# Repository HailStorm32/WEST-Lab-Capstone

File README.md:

## About

### Summary
This repo houses the code, board files, CAD files and documents for the SCuM observatory.

The SCuM observatory is designed as a portable platform that accommodates a SCuM breakout board alongside various measurement devices. These devices provide direct access to the SCuM’s I/O, enabling power control and monitoring, digital and analog pin stimulation/measurement, RF stimulation/measurement, and programming. All communication with the observatory, including control of its measurement devices, occurs through a single USB cable. A Python scripting interface is used for high-level interactions with the observatory and its hardware.

### Contributors
| Name                  |
|-----------------------|
| [Alex Jain](https://github.com/ajainPSU)   |
| [Demetri Van Sickle](https://github.com/HailStorm32) |
| [John Yang](https://github.com/yan7-psu)  |
| [Mitch Montee](https://github.com/mmontee)  |
|[Nate Sjullie](https://github.com/nsjullie) |

<br>

<br>

## Setup

Please see [The Wiki](https://github.com/HailStorm32/WEST-Lab-Capstone/wiki/2.0-Setup)

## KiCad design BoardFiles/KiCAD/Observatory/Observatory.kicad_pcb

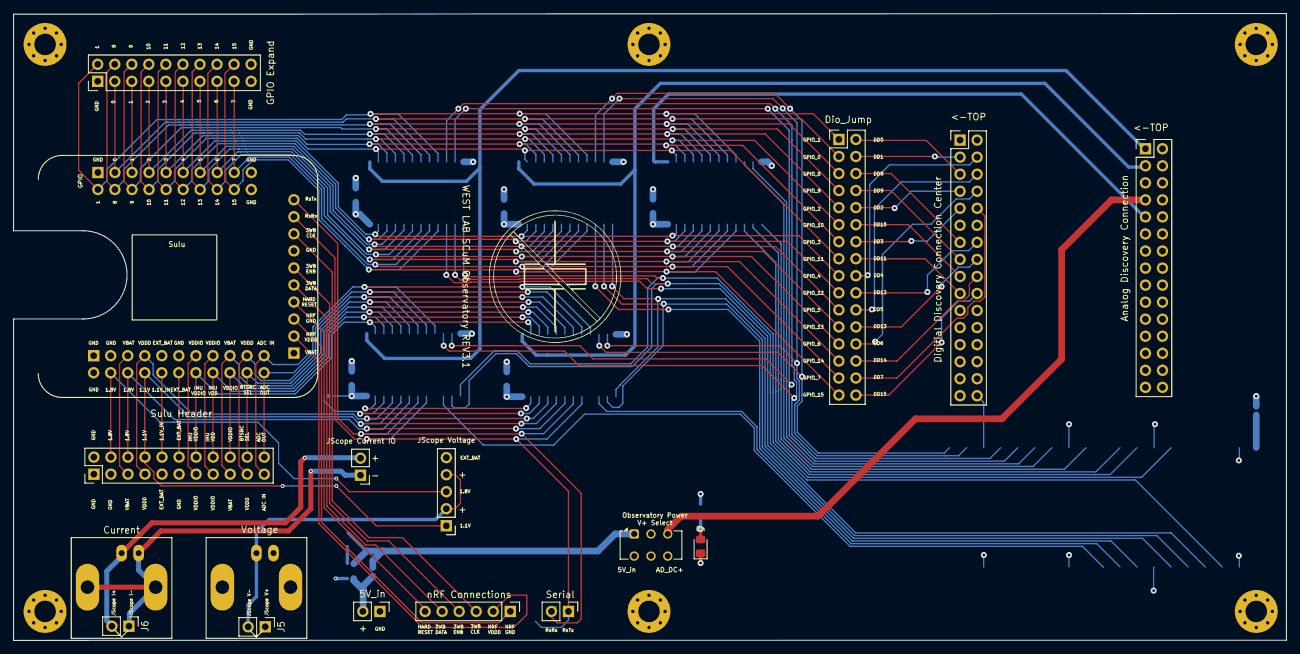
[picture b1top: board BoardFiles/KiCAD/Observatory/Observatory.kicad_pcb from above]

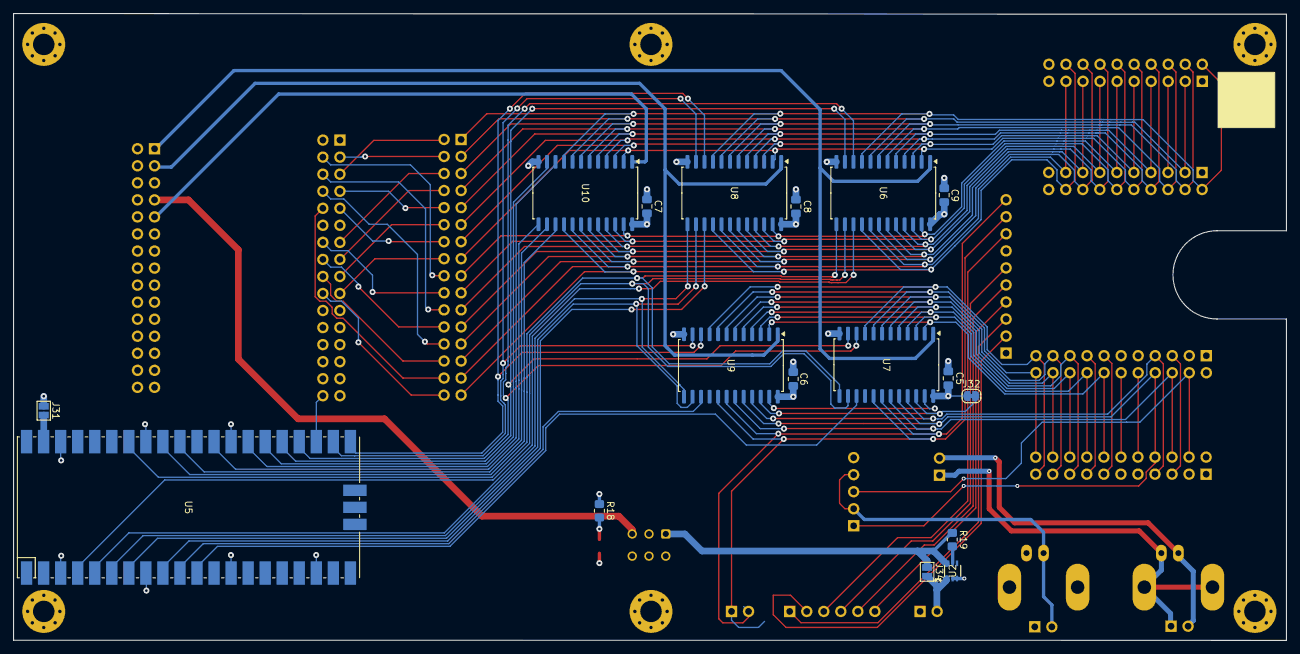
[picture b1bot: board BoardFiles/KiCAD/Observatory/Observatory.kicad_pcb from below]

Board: 4 copper layers, 189.7 x 93.4 mm, 40 parts (17 on the bottom side), 90 nets.

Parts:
C5, C6, C7, C8, C9: C; C_0805_2012Metric_Pad1.18x1.45mm_HandSolder
D1: LED; LED_0805_2012Metric_Pad1.15x1.40mm_HandSolder
J2: Analog Discovery Connection; PinHeader_2x15_P2.54mm_Vertical
J3: Digitial Discovery Connection Center; PinHeader_2x16_P2.54mm_Vertical
J4: GPIO Expand; PinHeader_2x10_P2.54mm_Vertical
J5: JScope V; PinHeader_1x02_P2.54mm_Vertical
J6: JScope I; PinHeader_1x02_P2.54mm_Vertical
J8: JScope Current IO; PinHeader_1x02_P2.54mm_Vertical
J9: 5V_in; PinHeader_1x02_P2.54mm_Vertical
J10: Dio_Jump; PinHeader_2x16_P2.54mm_Vertical
J11: nRF Connections; PinHeader_1x06_P2.54mm_Vertical
J12: Sulu Header; PinHeader_2x11_P2.54mm_Vertical
J13: Serial; PinHeader_1x02_P2.54mm_Vertical
J16: JScope Voltage; PinHeader_1x05_P2.54mm_Vertical
J20, J21, J22, J23, J36, J37: Mounting Hole; MountingHole_3.2mm_M3_Pad_Via
J24: Observatory PWR; SW_CK_JS202011CQN_DPDT_Straight
J30, J33: Conn_Coaxial_Small; BNC_Amphenol_B6252HB-NPP3G-50_Horizontal
J31, J34: Jumper; SolderJumper-2_P1.3mm_Open_Pad1.0x1.5mm
J32: Jumper; SolderJumper-2_P1.3mm_Bridged_RoundedPad1.0x1.5mm
R18: R; R_0805_2012Metric_Pad1.20x1.40mm_HandSolder
R19: R_st; R_0805_2012Metric_Pad1.20x1.40mm_HandSolder
U1: 1; SuLu_Foot
U2: LM66100DCKR
U5: Pico; RPi_Pico_SMD_TH
U6, U7, U8, U9, U10: CD74HC4067M; SOIC-24W_7.5x15.4mm_P1.27mm

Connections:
+5V: C5.1, C6.1, C7.1, C8.1, C9.1, J12.9, J12.12, J16.5, J24.2, J31.1, J32.1, R18.1, U1.9c (EXT_BAT), U1.12c (EXT_BAT), U6.24 (VCC), U7.24 (VCC), U8.24 (VCC), U9.24 (VCC), U10.24 (VCC)
AD_DC_Supply+: J2.7, J24.3
AD_Scope1+: J2.1, U6.1 (COM), U7.1 (COM)
AD_Scope1-: C5.2, C6.2, C7.2, C8.2, C9.2, D1.1 (K), J2.2, J2.4, J2.5, J2.6, J2.11, J2.12, J3.1, J3.2, J3.11, J3.12, J3.21, J3.22, J3.31, J3.32, J4.1, J4.19, J4.20, J5.1, J9.1, J12.1, J12.2, J12.3, J12.11, J20.1, J21.1, J22.1, J23.1, J33.2 (Ext), J36.1, J37.1, U1.1a (GND), U1.1c (GND), U1.2c (GND), U1.3c (GND), U1.7b (GND), U1.11c (GND), U1.19a (GND), U1.20a (GND), U2.2 (GND), U2.3 (*CE), U5.3 (GND), U5.8 (GND), U5.13 (GND), U5.18 (GND), U5.23 (GND), U5.28 (GND), U5.33 (AGND), U5.38 (GND), U6.12 (GND), U7.12 (GND), U8.12 (GND), U9.12 (GND), U10.12 (GND)
AD_Scope2+: J2.3, U8.1 (COM), U9.1 (COM)
AD_WaveGen1: J2.9, U10.1 (COM)
DD_DIN_0: J3.3, J10.4
DD_DIN_1: J3.5, J10.2
DD_DIN_2: J3.7, J10.10
DD_DIN_3: J3.9, J10.14
DD_DIN_4: J3.4, J10.18
DD_DIN_5: J3.6, J10.22
DD_DIN_6: J3.8, J10.26
DD_DIN_7: J3.10, J10.30
DD_DIN_8: J3.13, J10.6
DD_DIN_9: J3.15, J10.8
DD_DIN_10: J3.17, J10.12
DD_DIN_11: J3.19, J10.16
DD_DIN_12: J3.14, J10.20
DD_DIN_13: J3.16, J10.24
DD_DIN_14: J3.18, J10.28
DD_DIN_15: J3.20, J10.32
JS_I+: J6.2, J8.2, J30.1 (In)
JS_I-: J6.1, J8.1, J30.2 (Ext)
JS_V+: J5.2, J16.2, J16.4, J33.1 (In)
unnamed: D1.2 (A), R18.2
unnamed: J4.5, U1.5a (GPIO1)
unnamed: J11.1, U1.3b (NRF_GND)
unnamed: J11.2, U1.2b (NRF_VDDD)
unnamed: J11.3, U1.8b (3WB_CLK)
unnamed: J11.4, U1.6b (3WB_ENB)
unnamed: J11.5, U1.5b (3WB_DATA)
unnamed: J11.6, U1.4b (HARD_RESET)
unnamed: J12.4, J16.3, U1.4c (1.8V)
unnamed: J12.5, U1.5c (VBAT)
unnamed: J12.10, U1.10c (1.1V_IN)
unnamed: J12.13, U1.13c (VDDIO)
unnamed: J12.15, U1.15c (VDDIO)
unnamed: J24.1, J34.1, R19.1, U2.6 (VOUT)
unnamed: J31.2, U5.39 (VSYS)
unnamed: J9.2, J34.2, U2.1 (VIN)
unnamed: R19.2, U2.5 (ST)
Scope 1 Mux 1: J4.2, J10.1, U1.2a (GPIO1), U6.9 (I0), U8.9 (I0), U10.9 (I0)
Scope 1 Mux 2: J4.3, J10.3, U1.3a (GPIO0), U6.8 (I1), U8.8 (I1), U10.8 (I1)
Scope 1 Mux 3: J4.4, J10.5, U1.4a (GPIO8), U6.7 (I2), U8.7 (I2), U10.7 (I2)
Scope 1 Mux 4: J4.6, J10.7, U1.6a (GPIO9), U6.6 (I3), U8.6 (I3), U10.6 (I3)
Scope 1 Mux 5: J4.7, J10.9, U1.7a (GPIO2), U6.5 (I4), U8.5 (I4), U10.5 (I4)
Scope 1 Mux 6: J4.8, J10.11, U1.8a (GPIO10), U6.4 (I5), U8.4 (I5), U10.4 (I5)
Scope 1 Mux 7: J4.9, J10.13, U1.9a (GPIO3), U6.3 (I6), U8.3 (I6), U10.3 (I6)
Scope 1 Mux 8: J4.10, J10.15, U1.10a (GPIO11), U6.2 (I7), U8.2 (I7), U10.2 (I7)
Scope 1 Mux 9: J4.11, J10.17, U1.11a (GPIO4), U6.23 (I8), U8.23 (I8), U10.23 (I8)
Scope 1 Mux 10: J4.12, J10.19, U1.12a (GPIO12), U6.22 (I9), U8.22 (I9), U10.22 (I9)
Scope 1 Mux 11: J4.13, J10.21, U1.13a (GPIO5), U6.21 (I10), U8.21 (I10), U10.21 (I10)
Scope 1 Mux 12: J4.14, J10.23, U1.14a (GPIO13), U6.20 (I11), U8.20 (I11), U10.20 (I11)
Scope 1 Mux 13: J4.15, J10.25, U1.15a (GPIO6), U6.19 (I12), U8.19 (I12), U10.19 (I12)
Scope 1 Mux 14: J4.16, J10.27, U1.16a (GPIO14), U6.18 (I13), U8.18 (I13), U10.18 (I13)
Scope 1 Mux 15: J4.17, J10.29, U1.17a (GPIO7), U6.17 (I14), U8.17 (I14), U10.17 (I14)
Scope 1 Mux 16: J4.18, J10.31, U1.18a (GPIO15), U6.16 (I15), U8.16 (I15), U10.16 (I15)
Scope 1 Mux 17: J12.21, U1.21c (ADC_IN), U7.9 (I0), U9.9 (I0)
Scope 1 Mux 18: J12.22, U1.22c (ADC_OUT), U7.8 (I1), U9.8 (I1)
Scope 1 Mux 19: J12.19, U1.19c (VDDD), U7.7 (I2), U9.7 (I2)
Scope 1 Mux 20: J12.20, U1.20c (BTSRC_SEL), U7.6 (I3), U9.6 (I3)
Scope 1 Mux 21: J12.17, U1.17c (VBAT), U7.5 (I4), U9.5 (I4)
Scope 1 Mux 22: J12.18, U1.18c (VDDIO), U7.4 (I5), U9.4 (I5)
Scope 1 Mux 23: J12.16, U1.16c (IMU_VDD), U7.3 (I6), U9.3 (I6)
Scope 1 Mux 24: J12.14, U1.14c (IMU_VDDIO), U7.2 (I7), U9.2 (I7)
Scope 1 Mux 25: U7.23 (I8), U9.23 (I8)
Scope 1 Mux 26: J32.2, U7.22 (I9), U9.22 (I9)
Scope 1 Mux 27: J12.7, U1.7c (VDDD), U7.21 (I10), U9.21 (I10)
Scope 1 Mux 28: J12.8, J16.1, U1.8c (1.1V), U7.20 (I11), U9.20 (I11)
Scope 1 Mux 29: J12.6, U1.6c (1.8V), U7.19 (I12), U9.19 (I12)
Scope 1 Mux 30: J13.2, U1.10b (RsTx), U7.18 (I13), U9.18 (I13)
Scope 1 Mux 31: J13.1, U1.9b (RsRx), U7.17 (I14), U9.17 (I14)
Scope 1 Mux Control 0: U5.24 (GPIO18), U6.10 (S0), U7.10 (S0)
Scope 1 Mux Control 1: U5.25 (GPIO19), U6.11 (S1), U7.11 (S1)
Scope 1 Mux Control 2: U5.4 (GPIO2), U6.14 (S2), U7.14 (S2)
Scope 1 Mux Control 3: U5.34 (GPIO28_ADC2), U6.13 (S3), U7.13 (S3)
Scope 1 Mux ~EN_A: U5.5 (GPIO3), U6.15 (~E)
Scope 1 Mux ~EN_B: U5.11 (GPIO8), U7.15 (~E)
Scope 2 Mux Control 0: U5.21 (GPIO16), U8.10 (S0), U9.10 (S0)
Scope 2 Mux Control 1: U5.22 (GPIO17), U8.11 (S1), U9.11 (S1)
Scope 2 Mux Control 2: U5.7 (GPIO5), U8.14 (S2), U9.14 (S2)
Scope 2 Mux Control 3: U5.6 (GPIO4), U8.13 (S3), U9.13 (S3)
Scope 2 Mux ~EN_A: U5.9 (GPIO6), U8.15 (~E)
Scope 2 Mux ~EN_B: U5.10 (GPIO7), U9.15 (~E)
WaveGen. 1 Mux ~EN: U5.32 (GPIO27_ADC1), U10.15 (~E)
WaveGen. Mux Control 0: U5.27 (GPIO21), U10.10 (S0)
WaveGen. Mux Control 1: U5.26 (GPIO20), U10.11 (S1)
WaveGen. Mux Control 2: U5.31 (GPIO26_ADC0), U10.14 (S2)
WaveGen. Mux Control 3: U5.29 (GPIO22), U10.13 (S3)

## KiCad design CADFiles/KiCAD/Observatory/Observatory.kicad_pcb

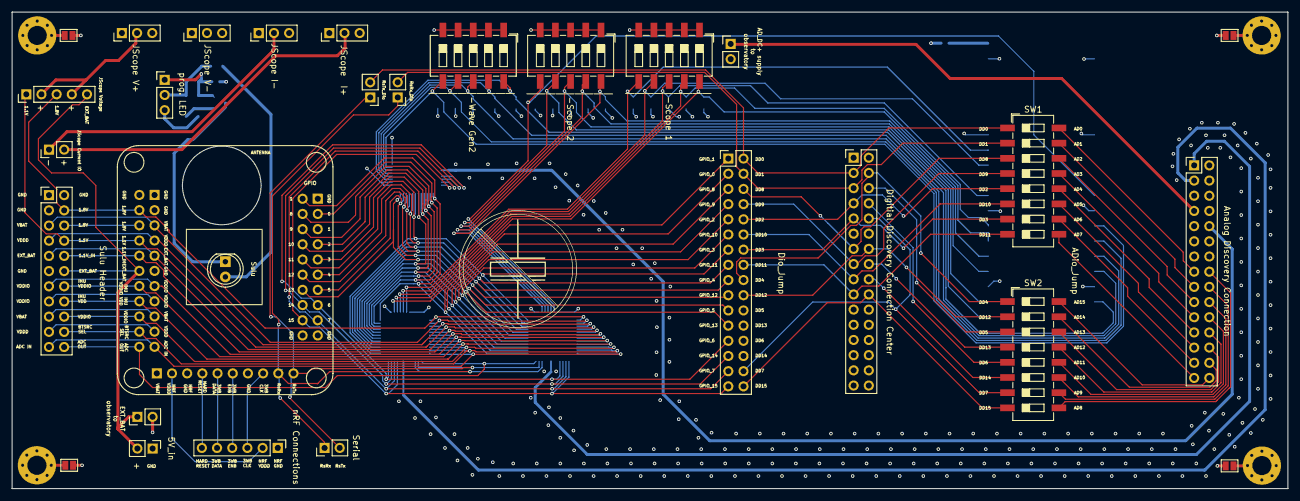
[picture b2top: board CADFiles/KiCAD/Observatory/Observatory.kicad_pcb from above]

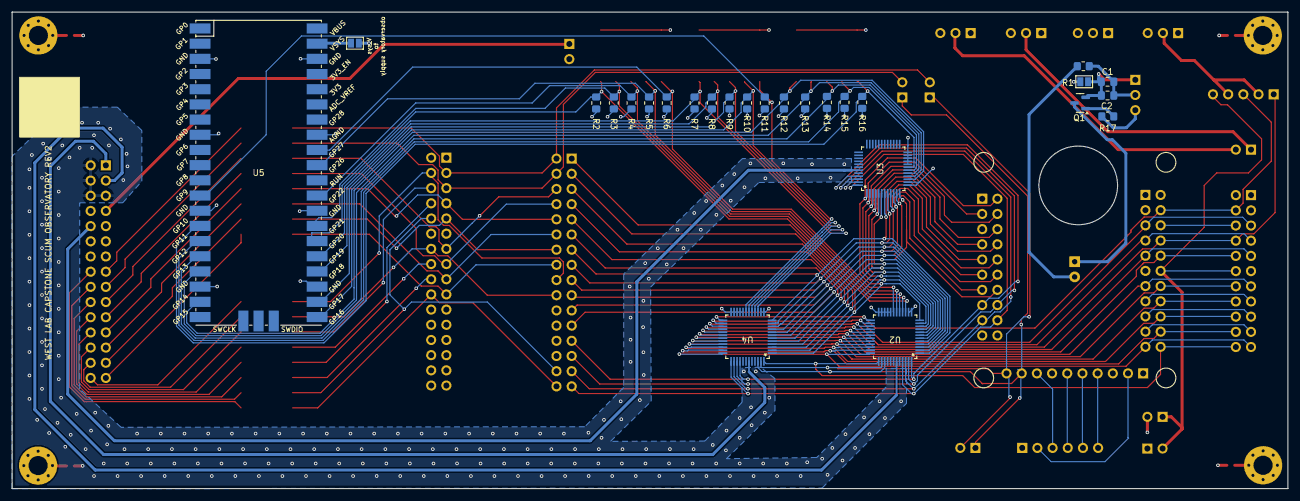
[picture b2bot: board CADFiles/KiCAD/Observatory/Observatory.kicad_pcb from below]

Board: 4 copper layers, 213.3 x 79.6 mm, 58 parts (26 on the bottom side), 108 nets.

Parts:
C1, C2: C; C_0805_2012Metric_Pad1.18x1.45mm_HandSolder
J1: GND/CUT; SolderJumper-2_P1.3mm_Open_Pad1.0x1.5mm
J2: Analog Discovery Connection; PinHeader_2x15_P2.54mm_Vertical
J3: Digitial Discovery Connection Center; PinHeader_2x16_P2.54mm_Vertical
J4: Scope 1 Mux Config.; SW_DIP_SPSTx05_Slide_6.7x14.26mm_W8.61mm_P2.54mm_LowProfile
J5: Scope 2 Mux Config.; SW_DIP_SPSTx05_Slide_6.7x14.26mm_W8.61mm_P2.54mm_LowProfile
J6: JScope V+; PinHeader_1x03_P2.54mm_Vertical
J7: JScope V-; PinHeader_1x03_P2.54mm_Vertical
J8: JScope Current IO; PinHeader_1x02_P2.54mm_Vertical
J9: 5V_in; PinHeader_1x02_P2.54mm_Vertical
J10: Dio_Jump; PinHeader_2x16_P2.54mm_Vertical
J11: nRF Connections; PinHeader_1x06_P2.54mm_Vertical
J12: Sulu Header; PinHeader_2x11_P2.54mm_Vertical
J13: Serial; PinHeader_1x02_P2.54mm_Vertical
J14: RsTx_Dio; PinHeader_1x02_P2.54mm_Vertical
J15: RsRx_Dio; PinHeader_1x02_P2.54mm_Vertical
J16: JScope Voltage; PinHeader_1x05_P2.54mm_Vertical
J17: WaveGen. 1 Mux Config.; SW_DIP_SPSTx05_Slide_6.7x14.26mm_W8.61mm_P2.54mm_LowProfile
J18: JScope I+; PinHeader_1x03_P2.54mm_Vertical
J19: JScope I-; PinHeader_1x03_P2.54mm_Vertical
J20, J21, J22, J23: Mounting Hole; MountingHole_3.2mm_M3_Pad_Via
J24: prog. LED; PinHeader_1x03_P2.54mm_Vertical
J25, J30: Jumper; PinHeader_1x02_P2.54mm_Vertical
J26, J27, J28, J29, J31: Jumper; SolderJumper-2_P1.3mm_Open_Pad1.0x1.5mm
Q1: 2N7002; SOT-23
R1: 14.7; R_0805_2012Metric_Pad1.20x1.40mm_HandSolder
R2, R3, R4, R5, R6, R7, R8, R9, R10, R11, R12, R13, R14, R15, R16: R_up; R_0805_2012Metric_Pad1.20x1.40mm_HandSolder
R17: 100k; R_0805_2012Metric_Pad1.20x1.40mm_HandSolder
SW1, SW2: SW_DIP_x08; SW_DIP_SPSTx08_Slide_6.7x21.88mm_W8.61mm_P2.54mm_LowProfile
U1: 1; SuLu_Foot
U2: Scope 1 Mux; SU_48_ADI
U3: Wave Gen. Mux; SU_48_ADI
U4: Scope 2 Mux; SU_48_ADI
U5: Pico; RPi_Pico_SMD_TH

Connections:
+5V: J25.2, J30.2, J31.1, R2.1, R3.1, R4.1, R5.1, R6.1, R7.1, R8.1, R9.1, R10.1, R11.1, R12.1, R13.1, R14.1, R15.1, R16.1, U2.13 (VDD), U2.14 (VDD), U3.13 (VDD), U3.14 (VDD), U4.13 (VDD), U4.14 (VDD)
AD_DIO_0: J2.15, SW1.16
AD_DIO_1: J2.17, SW1.15
AD_DIO_2: J2.19, SW1.14
AD_DIO_3: J2.21, SW1.13
AD_DIO_4: J2.23, SW1.12
AD_DIO_5: J2.25, SW1.11
AD_DIO_6: J2.27, SW1.10
AD_DIO_7: J2.29, SW1.9
AD_DIO_8: J2.16, SW2.9
AD_DIO_9: J2.18, SW2.10
AD_DIO_10: J2.20, SW2.11
AD_DIO_11: J2.22, SW2.12
AD_DIO_12: J2.24, SW2.13
AD_DIO_13: J2.26, SW2.14
AD_DIO_14: J2.28, SW2.15
AD_DIO_15: J2.30, SW2.16
AD_Scope1+: J2.1, U4.43 (D)
AD_Scope1-: J1.1, J2.2, J2.4, J2.5, J2.6, J2.11, J2.12, J3.1, J3.2, J3.11, J3.12, J3.21, J3.22, J3.31, J3.32, J4.1, J4.2, J4.3, J4.4, J4.5, J5.1, J5.2, J5.3, J5.4, J5.5, J7.2, J9.1, J11.1, J12.1, J12.2, J12.3, J12.11, J17.1, J17.2, J17.3, J17.4, J17.5, J26.1, J27.1, J28.1, J29.2, U1.1a (GND), U1.1c (GND), U1.2c (GND), U1.3b (NRF_GND), U1.3c (GND), U1.7b (GND), U1.11c (GND), U1.19a (GND), U1.20a (GND), U2.20 (CS*), U2.21 (WR*), U2.22 (EN*), U2.23 (GND), U2.24 (VSS), U3.20 (CS*), U3.21 (WR*), U3.22 (EN*), U3.23 (GND), U3.24 (VSS), U4.20 (CS*), U4.21 (WR*), U4.22 (EN*), U4.23 (GND), U4.24 (VSS), U5.3 (GND), U5.8 (GND), U5.13 (GND), U5.18 (GND), U5.23 (GND), U5.28 (GND), U5.33 (AGND), U5.38 (GND)
AD_Scope2+: J2.3, U2.43 (D)
AD_WaveGen2: J2.10, U3.43 (D)
DD_DIN_0: J3.3, J10.2, J14.2, SW1.1
DD_DIN_1: J3.5, J10.4, J15.2, SW1.2
DD_DIN_2: J3.7, J10.10, SW1.5
DD_DIN_3: J3.9, J10.14, SW1.7
DD_DIN_4: J3.4, J10.18, SW2.1
DD_DIN_5: J3.6, J10.22, SW2.3
DD_DIN_6: J3.8, J10.26, SW2.5
DD_DIN_7: J3.10, J10.30, SW2.7
DD_DIN_8: J3.13, J10.6, SW1.3
DD_DIN_9: J3.15, J10.8, SW1.4
DD_DIN_10: J3.17, J10.12, SW1.6
DD_DIN_11: J3.19, J10.16, SW1.8
DD_DIN_12: J3.14, J10.20, SW2.2
DD_DIN_13: J3.16, J10.24, SW2.4
DD_DIN_14: J3.18, J10.28, SW2.6
DD_DIN_15: J3.20, J10.32, SW2.8
JS_I+: J8.2, J18.2
JS_I-: J8.1, J19.2
JS_V+: J6.2, J16.2, J16.4
unnamed: C1.1, C2.1, J1.2, J24.1, Q1.2 (S)
unnamed: J2.7, J25.1
unnamed: J11.2, U1.2b (NRF_VDDD)
unnamed: J11.3, U1.8b (3WB_CLK)
unnamed: J11.4, U1.6b (3WB_ENB)
unnamed: J11.5, U1.5b (3WB_DATA)
unnamed: J11.6, U1.4b (HARD_RESET)
unnamed: J12.6, U1.6c (1.8V)
unnamed: J9.2, J12.12, J16.5, J30.1, U1.12c (EXT_BAT)
unnamed: J12.15, U1.15c (VDDIO)
unnamed: J12.17, U1.17c (VBAT)
unnamed: J12.19, U1.19c (VDDD)
unnamed: J20.1, J26.2
unnamed: J21.1, J27.2
unnamed: J22.1, J28.2
unnamed: J23.1, J29.1
unnamed: C1.2, C2.2, J24.2, R1.1
unnamed: J24.3, R17.1
unnamed: J31.2, U5.39 (VSYS)
unnamed: Q1.3 (D), U1.1e (1_led)
unnamed: Q1.1 (G), R17.2
unnamed: R1.2, U1.2e (2_led)
Scope 1 Mux 1: J10.1, U1.2a (GPIO1), U2.12 (S1), U3.1 (S12), U4.1 (S12)
Scope 1 Mux 2: J10.3, U1.3a (GPIO0), U2.11 (S2), U3.2 (S11), U4.2 (S11)
Scope 1 Mux 3: J10.5, U1.4a (GPIO8), U2.10 (S3), U3.3 (S10), U4.3 (S10)
Scope 1 Mux 4: J10.7, U1.6a (GPIO9), U2.9 (S4), U3.4 (S9), U4.4 (S9)
Scope 1 Mux 5: J10.9, U1.7a (GPIO2), U2.8 (S5), U3.5 (S8), U4.5 (S8)
Scope 1 Mux 6: J10.11, U1.8a (GPIO10), U2.7 (S6), U3.6 (S7), U4.6 (S7)
Scope 1 Mux 7: J10.23, U1.14a (GPIO13), U2.6 (S7), U3.12 (S1), U4.7 (S6)
Scope 1 Mux 8: J10.21, U1.13a (GPIO5), U2.5 (S8), U3.11 (S2), U4.8 (S5)
Scope 1 Mux 9: J10.19, U1.12a (GPIO12), U2.4 (S9), U3.10 (S3), U4.9 (S4)
Scope 1 Mux 10: J10.17, U1.11a (GPIO4), U2.3 (S10), U3.9 (S4), U4.10 (S3)
Scope 1 Mux 11: J10.15, U1.10a (GPIO11), U2.2 (S11), U3.8 (S5), U4.11 (S2)
Scope 1 Mux 12: J10.13, U1.9a (GPIO3), U2.1 (S12), U3.7 (S6), U4.12 (S1)
Scope 1 Mux 13: J10.25, U1.15a (GPIO6), U2.48 (S13), U3.45 (S16), U4.40 (S32)
Scope 1 Mux 14: J10.27, U1.16a (GPIO14), U2.47 (S14), U3.46 (S15), U4.39 (S31)
Scope 1 Mux 15: J10.29, U1.17a (GPIO7), U2.46 (S15), U3.47 (S14), U4.38 (S30)
Scope 1 Mux 16: J10.31, U1.18a (GPIO15), U2.45 (S16), U3.48 (S13), U4.37 (S29)
Scope 1 Mux 17: J12.4, J16.3, U1.4c (1.8V), U2.25 (S17), U4.25 (S17)
Scope 1 Mux 18: J12.5, U1.5c (VBAT), U2.26 (S18), U4.26 (S18)
Scope 1 Mux 19: J12.7, U1.7c (VDDD), U2.27 (S19), U4.27 (S19)
Scope 1 Mux 20: J12.8, J16.1, U1.8c (1.1V), U2.28 (S20), U4.28 (S20)
Scope 1 Mux 21: J12.9, U1.9c (EXT_BAT), U2.29 (S21), U4.29 (S21)
Scope 1 Mux 22: J12.10, U1.10c (1.1V_IN), U2.30 (S22), U4.30 (S22)
Scope 1 Mux 23: J12.13, U1.13c (VDDIO), U2.31 (S23), U4.31 (S23)
Scope 1 Mux 24: J12.14, U1.14c (IMU_VDDIO), U2.32 (S24), U4.32 (S24)
Scope 1 Mux 25: J12.16, U1.16c (IMU_VDD), U2.33 (S25), U4.33 (S25)
Scope 1 Mux 26: J12.18, U1.18c (VDDIO), U2.34 (S26), U4.34 (S26)
Scope 1 Mux 27: J12.20, U1.20c (BTSRC_SEL), U2.35 (S27), U4.35 (S27)
Scope 1 Mux 28: J12.21, U1.21c (ADC_IN), U2.36 (S28), U4.36 (S28)
Scope 1 Mux 29: J12.22, U1.22c (ADC_OUT), U2.37 (S29), U4.48 (S13)
Scope 1 Mux 30: J13.2, J14.1, U1.10b (RsTx), U2.38 (S30), U4.47 (S14)
Scope 1 Mux 31: J13.1, J15.1, U1.9b (RsRx), U2.39 (S31), U4.46 (S15)
Scope 1 Mux Control 0: J4.10, R2.2, U2.15 (A0), U5.26 (GPIO20)
Scope 1 Mux Control 1: J4.9, R3.2, U2.16 (A1), U5.27 (GPIO21)
Scope 1 Mux Control 2: J4.8, R4.2, U2.17 (A2), U5.29 (GPIO22)
Scope 1 Mux Control 3: J4.7, R5.2, U2.18 (A3), U5.31 (GPIO26_ADC0)
Scope 1 Mux Control 4: J4.6, R6.2, U2.19 (A4), U5.32 (GPIO27_ADC1)
Scope 2 Mux Control 0: J5.10, R7.2, U4.15 (A0), U5.25 (GPIO19)
Scope 2 Mux Control 1: J5.9, R8.2, U4.16 (A1), U5.24 (GPIO18)
Scope 2 Mux Control 2: J5.8, R9.2, U4.17 (A2), U5.22 (GPIO17)
Scope 2 Mux Control 3: J5.7, R10.2, U4.18 (A3), U5.21 (GPIO16)
Scope 2 Mux Control 4: J5.6, R11.2, U4.19 (A4), U5.12 (GPIO9)
WaveGen. Mux Control 0: J17.10, R12.2, U3.15 (A0), U5.19 (GPIO14)
WaveGen. Mux Control 1: J17.9, R13.2, U3.16 (A1), U5.17 (GPIO13)
WaveGen. Mux Control 2: J17.8, R14.2, U3.17 (A2), U5.16 (GPIO12)
WaveGen. Mux Control 3: J17.7, R15.2, U3.18 (A3), U5.15 (GPIO11)
WaveGen. Mux Control 4: J17.6, R16.2, U3.19 (A4), U5.14 (GPIO10)

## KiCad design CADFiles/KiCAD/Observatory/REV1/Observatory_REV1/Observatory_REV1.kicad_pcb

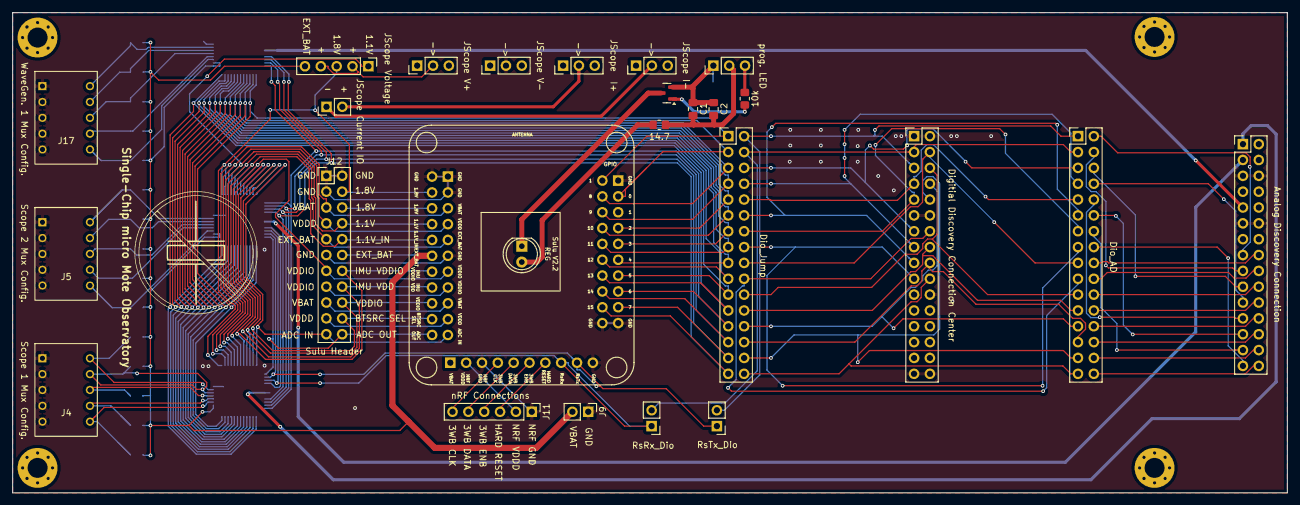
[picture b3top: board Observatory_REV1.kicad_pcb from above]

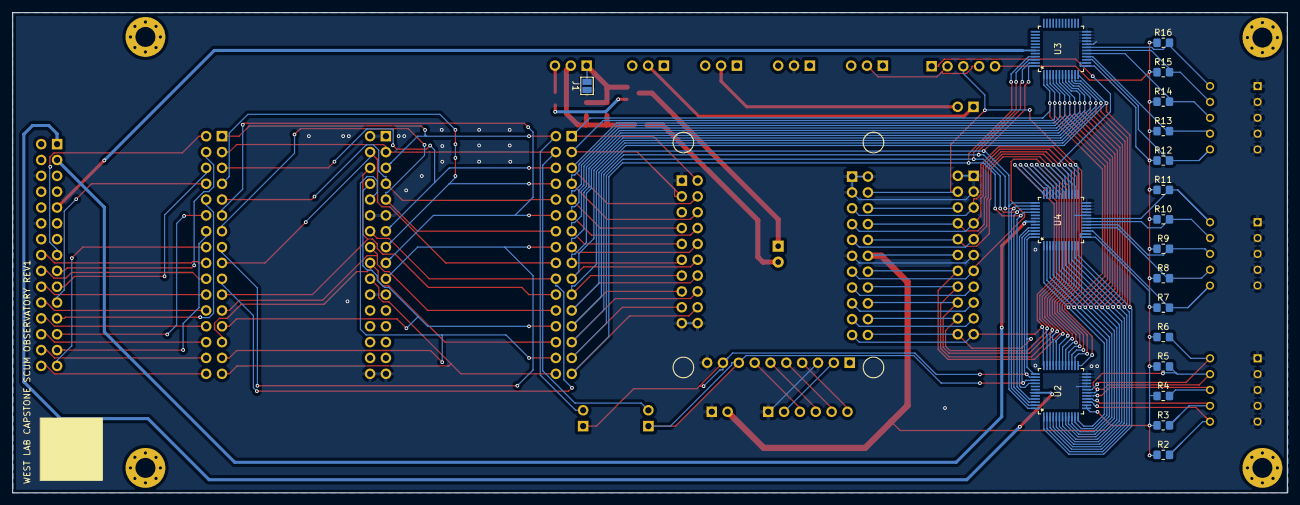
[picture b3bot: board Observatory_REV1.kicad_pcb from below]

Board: 2 copper layers, 204.4 x 77.0 mm, 48 parts (19 on the bottom side), 102 nets.

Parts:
10k: 100k; R_0805_2012Metric_Pad1.20x1.40mm_HandSolder
C1, C2: C; C_0805_2012Metric_Pad1.18x1.45mm_HandSolder
J1: GND/CUT; SolderJumper-2_P1.3mm_Open_Pad1.0x1.5mm
J2: Analog Discovery Connection; PinHeader_2x15_P2.54mm_Vertical
J3: Digitial Discovery Connection Center; PinHeader_2x16_P2.54mm_Vertical
J4: Scope 1 Mux Config.; DIP8_208-5_CTS
J5: Scope 2 Mux Config.; DIP8_208-5_CTS
J6: JScope V+; PinHeader_1x03_P2.54mm_Vertical
J7: JScope V-; PinHeader_1x03_P2.54mm_Vertical
J8: JScope Current IO; PinHeader_1x02_P2.54mm_Vertical
J9: 5V_in; PinHeader_1x02_P2.54mm_Vertical
J10: Dio_Jump; PinHeader_2x16_P2.54mm_Vertical
J11: nRF Connections; PinHeader_1x06_P2.54mm_Vertical
J12: Sulu Header; PinHeader_2x11_P2.54mm_Vertical
J13: Dio_AD; PinHeader_2x16_P2.54mm_Vertical
J14: RsTx_Dio; PinHeader_1x02_P2.54mm_Vertical
J15: RsRx_Dio; PinHeader_1x02_P2.54mm_Vertical
J16: JScope Voltage; PinHeader_1x05_P2.54mm_Vertical
J17: WaveGen. 1 Mux Config.; DIP8_208-5_CTS
J18: JScope I+; PinHeader_1x03_P2.54mm_Vertical
J19: JScope I-; PinHeader_1x03_P2.54mm_Vertical
J20, J21, J22, J23: Mounting Hole; MountingHole_3.2mm_M3_Pad_Via
J24: prog. LED; PinHeader_1x03_P2.54mm_Vertical
Q1: 2N7002; SOT-23
R1: 14.7; R_0805_2012Metric_Pad1.20x1.40mm_HandSolder
R2, R3, R4, R5, R6, R7, R8, R9, R10, R11, R12, R13, R14, R15, R16: R_up; R_0805_2012Metric_Pad1.20x1.40mm_HandSolder
U1: 1; SuLu_Foot
U2: Scope 1 Mux; SU_48_ADI
U3: Wave Gen. Mux; SU_48_ADI
U4: Scope 2 Mux; SU_48_ADI

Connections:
+5V: J9.2, J12.12, J16.5, R2.1, R3.1, R4.1, R5.1, R6.1, R7.1, R8.1, R9.1, R10.1, R11.1, R12.1, R13.1, R14.1, R15.1, R16.1, U1.12c (EXT_BAT), U2.13 (VDD), U2.14 (VDD), U3.13 (VDD), U3.14 (VDD), U4.13 (VDD), U4.14 (VDD)
AD_DIO_0: J2.15, J13.2
AD_DIO_1: J2.17, J13.4
AD_DIO_2: J2.19, J13.6
AD_DIO_3: J2.21, J13.8
AD_DIO_4: J2.23, J13.10
AD_DIO_5: J2.25, J13.12
AD_DIO_6: J2.27, J13.14
AD_DIO_7: J2.29, J13.16
AD_DIO_8: J2.16, J13.18
AD_DIO_9: J2.18, J13.20
AD_DIO_10: J2.20, J13.22
AD_DIO_11: J2.22, J13.24
AD_DIO_12: J2.24, J13.26
AD_DIO_13: J2.26, J13.28
AD_DIO_14: J2.28, J13.30
AD_DIO_15: J2.30, J13.32
AD_Scope1+: J2.1, U2.43 (D)
AD_Scope2+: J2.3, U4.43 (D)
AD_WaveGen1: J2.9, U3.43 (D)
DD_DIN_0: J3.3, J10.4, J13.3, J15.2
DD_DIN_1: J3.5, J10.2, J13.1, J14.2
DD_DIN_2: J3.7, J10.10, J13.9
DD_DIN_3: J3.9, J10.14, J13.13
DD_DIN_4: J3.4, J10.18, J13.17
DD_DIN_5: J3.6, J10.22, J13.21
DD_DIN_6: J3.8, J10.26, J13.25
DD_DIN_7: J3.10, J10.30, J13.29
DD_DIN_8: J3.13, J10.6, J13.5
DD_DIN_9: J3.15, J10.8, J13.7
DD_DIN_10: J3.17, J10.12, J13.11
DD_DIN_11: J3.19, J10.16, J13.15
DD_DIN_12: J3.14, J10.20, J13.19
DD_DIN_13: J3.16, J10.24, J13.23
DD_DIN_14: J3.18, J10.28, J13.27
DD_DIN_15: J3.20, J10.32, J13.31
JS_I+: J8.2, J18.2
JS_I-: J8.1, J19.2
JS_V+: J6.2, J16.2, J16.4
JS_V-: J1.1, J2.5, J2.6, J2.11, J2.12, J3.1, J3.2, J3.11, J3.12, J3.21, J3.22, J3.31, J3.32, J4.1, J4.2, J4.3, J4.4, J4.5, J5.1, J5.2, J5.3, J5.4, J5.5, J7.2, J9.1, J11.1, J12.1, J12.2, J12.3, J12.11, J17.1, J17.2, J17.3, J17.4, J17.5, U1.1a (GND), U1.1c (GND), U1.2c (GND), U1.3b (NRF_GND), U1.3c (GND), U1.10b (GND), U1.11c (GND), U1.19a (GND), U1.20a (GND), U2.20 (CS*), U2.21 (WR*), U2.22 (EN*), U2.23 (GND), U2.24 (VSS), U3.20 (CS*), U3.21 (WR*), U3.22 (EN*), U3.23 (GND), U3.24 (VSS), U4.20 (CS*), U4.21 (WR*), U4.22 (EN*), U4.23 (GND), U4.24 (VSS)
unnamed: C1.1, C2.1, J1.2, J24.1, Q1.2 (S)
unnamed: J11.2, U1.2b (NRF_VDDD)
unnamed: J11.3, U1.7b (HARD_RESET)
unnamed: J11.4, U1.6b (3WB_ENB)
unnamed: J11.5, U1.5b (3WB_DATA)
unnamed: J11.6, U1.4b (3WB_CLK)
unnamed: J12.6, U1.6c (1.8V)
unnamed: J12.15, U1.15c (VDDIO)
unnamed: J12.17, U1.17c (VBAT)
unnamed: J12.19, U1.19c (VDDD)
unnamed: C1.2, C2.2, J24.2, R1.1
unnamed: 10k.1, J24.3
unnamed: Q1.3 (D), U1.1e (1_led)
unnamed: 10k.2, Q1.1 (G)
unnamed: R1.2, U1.2e (2_led)
Scope 1 Mux 1: J10.1, U1.2a (GPIO1), U2.12 (S1), U3.1 (S12), U4.1 (S12)
Scope 1 Mux 2: J10.3, U1.3a (GPIO0), U2.11 (S2), U3.2 (S11), U4.2 (S11)
Scope 1 Mux 3: J10.5, U1.4a (GPIO8), U2.10 (S3), U3.3 (S10), U4.3 (S10)
Scope 1 Mux 4: J10.7, U1.6a (GPIO9), U2.9 (S4), U3.4 (S9), U4.4 (S9)
Scope 1 Mux 5: J10.9, U1.7a (GPIO2), U2.8 (S5), U3.5 (S8), U4.5 (S8)
Scope 1 Mux 6: J10.11, U1.8a (GPIO10), U2.7 (S6), U3.6 (S7), U4.6 (S7)
Scope 1 Mux 7: J10.13, U1.9a (GPIO3), U2.6 (S7), U3.7 (S6), U4.7 (S6)
Scope 1 Mux 8: J10.15, U1.10a (GPIO11), U2.5 (S8), U3.8 (S5), U4.8 (S5)
Scope 1 Mux 9: J10.17, U1.11a (GPIO4), U2.4 (S9), U3.9 (S4), U4.9 (S4)
Scope 1 Mux 10: J10.19, U1.12a (GPIO12), U2.3 (S10), U3.10 (S3), U4.10 (S3)
Scope 1 Mux 11: J10.21, U1.13a (GPIO5), U2.2 (S11), U3.11 (S2), U4.11 (S2)
Scope 1 Mux 12: J10.23, U1.14a (GPIO13), U2.1 (S12), U3.12 (S1), U4.12 (S1)
Scope 1 Mux 13: J10.25, U1.15a (GPIO6), U2.48 (S13), U3.48 (S13), U4.37 (S29)
Scope 1 Mux 14: J10.27, U1.16a (GPIO14), U2.47 (S14), U3.47 (S14), U4.38 (S30)
Scope 1 Mux 15: J10.29, U1.17a (GPIO7), U2.46 (S15), U3.46 (S15), U4.39 (S31)
Scope 1 Mux 16: J10.31, U1.18a (GPIO15), U2.45 (S16), U3.45 (S16), U4.40 (S32)
Scope 1 Mux 17: J12.4, J16.3, U1.4c (1.8V), U2.25 (S17), U4.25 (S17)
Scope 1 Mux 18: J12.5, U1.5c (VBAT), U2.26 (S18), U4.26 (S18)
Scope 1 Mux 19: J12.7, U1.7c (VDDD), U2.27 (S19), U4.27 (S19)
Scope 1 Mux 20: J12.8, J16.1, U1.8c (1.1V), U2.28 (S20), U4.28 (S20)
Scope 1 Mux 21: J12.9, U1.9c (EXT_BAT), U2.29 (S21), U4.29 (S21)
Scope 1 Mux 22: J12.10, U1.10c (1.1V_IN), U2.30 (S22), U4.30 (S22)
Scope 1 Mux 23: J12.13, U1.13c (VDDIO), U2.31 (S23), U4.31 (S23)
Scope 1 Mux 24: J12.14, U1.14c (IMU_VDDIO), U2.32 (S24), U4.32 (S24)
Scope 1 Mux 25: J12.16, U1.16c (IMU_VDD), U2.33 (S25), U4.33 (S25)
Scope 1 Mux 26: J12.18, U1.18c (VDDIO), U2.34 (S26), U4.34 (S26)
Scope 1 Mux 27: J12.20, U1.20c (BTSRC_SEL), U2.35 (S27), U4.35 (S27)
Scope 1 Mux 28: J12.21, U1.21c (ADC_IN), U2.36 (S28), U4.36 (S28)
Scope 1 Mux 29: J12.22, U1.22c (ADC_OUT), U2.37 (S29), U4.48 (S13)
Scope 1 Mux 30: J14.1, U1.9b (RsTx), U2.38 (S30), U4.47 (S14)
Scope 1 Mux 31: J15.1, U1.8b (RsRx), U2.39 (S31), U4.46 (S15)
Scope 1 Mux 32: U2.40 (S32), U4.45 (S16)
Scope 1 Mux Control 0: J4.10, R2.2, U2.15 (A0)
Scope 1 Mux Control 1: J4.9, R3.2, U2.16 (A1)
Scope 1 Mux Control 2: J4.8, R4.2, U2.17 (A2)
Scope 1 Mux Control 3: J4.7, R5.2, U2.18 (A3)
Scope 1 Mux Control 4: J4.6, R6.2, U2.19 (A4)
Scope 2 Mux Control 0: J5.10, R7.2, U4.15 (A0)
Scope 2 Mux Control 1: J5.9, R8.2, U4.16 (A1)
Scope 2 Mux Control 2: J5.8, R9.2, U4.17 (A2)
Scope 2 Mux Control 3: J5.7, R10.2, U4.18 (A3)
Scope 2 Mux Control 4: J5.6, R11.2, U4.19 (A4)
WaveGen. Mux Control 0: J17.10, R12.2, U3.15 (A0)
WaveGen. Mux Control 1: J17.9, R13.2, U3.16 (A1)
WaveGen. Mux Control 2: J17.8, R14.2, U3.17 (A2)
WaveGen. Mux Control 3: J17.7, R15.2, U3.18 (A3)
WaveGen. Mux Control 4: J17.6, R16.2, U3.19 (A4)

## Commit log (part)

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2025-01-25 init commit
2025-01-25 add .gitignore to exclude environment directory
2025-01-25 add initial setup script and requirements file
2025-01-25 updated directory naming
2025-01-25 Undo weird NTFS file shenanigans
2025-01-26 Added submodule for Digilent API
2025-01-27 Update README for submodule setup
2025-01-29 Push for review
    Rev1 PCB needs review.
2025-01-29 Clean up
2025-01-30 Add PDFs
2025-02-02 begin dir structure layout
2025-02-02 Update submodule path for Digilent API
2025-02-03 remove submodule
2025-02-03 Add back submodule
2025-02-03 Add example scripts folder
2025-02-06 Add layout
2025-02-06 Update .gitignore to include .vscode directory
2025-02-06 Rename doxygen folder to DoxygenOutput in setup_env.bat
2025-02-07 Added pyjoulescope as a submodule
2025-02-07 Add YKUSH repository as submodule.
    02/07/2025 - 10:49 AM GMT -8
    Adding YKUSH repository as a submodule into the Vendors API folder.
2025-02-07 RF Explorer submodule
2025-02-08 Removed testAPI
2025-02-08 Add pyjoulescope as a submodule
2025-02-09 added digi_disc sample
2025-02-09 push digital example script
2025-02-12 Update requirements.txt to include matplotlib dependency
2025-02-12 Begin AD2 sample script
2025-02-12 mess around with timed capture
2025-02-12 add waveform and scope example
2025-02-12 Add Pattern generator example
2025-02-13 Added print header
2025-02-13 Added AD2 example script
2025-02-16 Joule Scope init commit
2025-02-16 Add files via upload
    Yepkit control module script.
    Note that you do need ykush's software and executable to be able to run this script. In addition a valid path to the executable needs to be present.
    The executable needs the .dll file, the .exe, and .bat file in order to run.
    Power cycling functions can be edited in terms of time requirements at a later date. This script is fully functional and has undergone numerous validation and verification tests.
2025-02-18 Add directory for validation script
2025-02-19 Added directory for C source and binary
2025-02-22 Added validation script
2025-02-22 Added analog tests
2025-02-23 update validation
    added serial baud rate tester, minor rev to digital.py
2025-02-28 Tests now start via a ping from SCuM
2025-02-28 removed debug variable
2025-02-28 remove trigger use from digital script
2025-02-28 Add delay for powerup
2025-02-28 temp change for running without DD
2025-02-28 correct typos in comments
2025-03-02 Moved binary to bin folder and updated path
2025-03-02 Add serial package to requirements
2025-03-02 Fix variable scope issue
2025-03-02 Fix formatting in test list for consistency
2025-03-02 Update Serial_Baud_Test.py
    now takes parameter
2025-03-03 Add files via upload
    Initial test of the joulescope/yepkit.
    No threading/queues involved yet, testing if joulescope can read values from scum and output into a file.
2025-03-03 Update requirements to replace serial with pyserial
2025-03-03 Comment out unused test cases and add power-up wait message
2025-03-03 Close serial port and exit gracefully in scumProgram
2025-03-03 added SCuM test .C/.bin
2025-03-03 Update powertest1.py
    - Added additional parameters from joulescope example.
    - Fixed several syntax errors.
    - Verified if parse_argument, process_argument, and statisics_callback were needed.
    - Included simple user interface to trigger the power_cycle and joulescope.
    - Included output_type if/else statement.
2025-03-03 new C script
2025-03-03 Addition of temporary print results
2025-03-04 Integrate changes found during testing
2025-03-05 Add scope continuous read
2025-03-05 Getting somewhere
2025-03-05 Update and rename powertest1.py to powertest1b.py
    - Fixed several syntax errors
    - Confirmation that it works to power cycle and can read joulescope values
    - Outputs into a text file.
2025-03-07 Added config file and way to easily switch between AD2 and DD
2025-03-07 Added trigger and nRF COM port to config
2025-03-07 Add framework for running spectrum analyzer self test
2025-03-10 added testing
2025-03-10 Update default for AD2_FOR_DIGITAL to False
2025-03-10 Add analog test configuration parameters to Config.py
2025-03-10 Update master script to work with joule scope changes
2025-03-10 Begin REV 2
2025-03-10 Update powertest1b.py
    - Removed unnecessary measurements.
    - Development comments added for modification.
2025-03-10 Update powertest1b.py
    - Fixed syntax errors
2025-03-15 Rewrote continuous capture function
2025-03-15 Add clock signal test
2025-03-15 Updated self test to measure more frequencies
2025-03-15 Add comments to clarify the CLOCKS_TO_TEST configuration
2025-03-15 Refactor voltage validation tests to include measured voltage values and adjust clock tolerance settings
2025-03-15 Enhance frequency determination function with improved accuracy checks and sample rate handling
2025-03-15 Prep for merge to master
2025-03-15 Add clock measure test and rewrite scope continuous capture
2025-03-16 Added beginnings of git validation script
2025-03-16 Update README.md to enhance setup instructions and clarify environment requirements
2025-03-21 All nets routed.
2025-03-21 DRC pass. Labels Added.
2025-03-21 ADD REV2 PDFs
2025-03-22 AD DC(-) error fixed. Jumpers added for feet grounds and DC supplies
2025-03-26 Add support for testing multiple binaries
2025-03-26 Update scumProgram to take binary path and update name to scum_program
2025-03-26 Added storing of test results
2025-03-26 Update requirements.txt
    Including libraries needed for interfacing with Adalm Pluto SDR.
2025-03-26 Update requirements.txt
    Correcting "=" to "==".
2025-03-26 Update README.md
    Added information to customize IP address of Adalm-Pluto SDRs.
2025-03-26 Add files via upload
    Uploading current RF python file.
2025-03-26 Update SCuM script to include AD clock test and RF TX sweep. Add seperate .bin for each test.
2025-03-27 Update scum_program to return a test result
2025-03-28 Add support for multiple tests
2025-03-29 Move to a common test results structure
2025-03-29 Add flag to track changes detected for validation report generation
2025-03-29 clean up comments
2025-03-30 Add HTML report generation for test results
2025-03-30 fix imports
2025-03-31 Update and rename powertest1e.py to powertest1f.py
    - Added Threading
    - Added structural format for results
    - Last to do is just test and compare it with actual desired values for the tests
2025-04-02 main.py -> pico.
2025-04-05 Support for [x,y] pair graphs and paths to graph images
2025-04-06 Refactor report gen to be more maintainable and support multiple graphs per sub test
2025-04-06 update structure of report gen verification
2025-04-06 Update axis label references in report generation and validation code
2025-04-09 Updated for Rev2 PCB. Changed to C development. Drag and drop .uf2 file for pico.
2025-04-10 Add support for pico calls
2025-04-10 Moved to one set of device handles
2025-04-10 Added support for new radio test structure
2025-04-10 Add files via upload
    Self-test updated to include improved bit-error-rate test.
2025-04-10 Updated self-test return values to new format.
2025-04-10 REV_2.1. PDFs updated. RsTx pin fix. LEDs added. BNC option added.
2025-04-15 Add command for mux usage
2025-04-15 Integrate joulescope functions for power consumption monitoring
2025-04-15 new .bins added
2025-04-16 Remove pico stubs
2025-04-18 Add files via upload
    Updated self test returned results, added folder for storing timestamped folders for RF data, updated scum test to return image path to generated PSD .png file.
2025-04-18 Remove doxygen folder creation from setup_env.bat and update comments accordingly
2025-04-18 Remove DoxygenOutput directory from .gitignore
2025-04-18 Update .gitignore and setup_env.bat to include ResultBackups folder
2025-04-18 Update joulescopetest.py
    - Added CSV file handling. This has a default file path if none is stated, check note in header.
    - Added various error handling throughout program.
    - Added ResultsBackup handling.
2025-04-18 Update joulescopetest.py
    - Removed sys module, not used anywhere.
2025-04-21 LED circuit fix, added decoupling cap
2025-04-22 Changes for new USB hub and fix typo with trigger pin
2025-04-22 fix incorrect mux command for 1.8V pin
2025-04-22 Changes found during testing
2025-04-23 added configurable VIO
2025-04-23 New .bins
2025-04-24 adjust delays
2025-04-25 Fixed intermittent self-test failure.
2025-04-25 Integrate serial test into Validation script
2025-04-25 Update submodule URL for WaveForms SDK to point to fork
2025-04-25 Corrected returning results and image path.
2025-04-25 testing changes
2025-04-25 adjust frequency tolerances in Config.py
2025-04-25 Adjusted joulescope value reporting
2025-04-25 Clarify measurement units in validation output for reference voltages and clock signals
2025-04-25 Added trigger channel back to logic analysis tests
2025-04-25 Reset the the mux in the main script
2025-04-25 Add current range thresholds to stop_joulescope function and update reporting units
2025-04-26 Update Joulescope acceptable voltage and current ranges
2025-04-26 renamed git_validation to nightly_validation
2025-04-26 Remove obsolete stub functions and clean up main script output
2025-04-26 Remove unused import and clean up comments in Config.py
2025-04-26 Add configuration template for validation tests, Config.py is now untracked and setup script will copy over template
2025-04-27 Add check for ResultsBackups directory in validation scripts
2025-04-27 Untrack Config.py
2025-04-27 Fix typo in ResultsBackups directory check in Nightly_Validation.py
2025-04-27 Fix directory name typo in SCuMValidation.py
2025-04-27 Add email report functionality and PDF generation to validation scripts
2025-04-28 update pluto tests
2025-04-28 Replace stub self-check with RF self-test in scum_validation.py
2025-04-28 Rename Nightly_Validation.py to nightly_validation.py
2025-04-28 Add values to return structure in RF_tx_rx_tests.py
2025-04-29 Add pandas to requirements.txt
2025-04-29 Fix import statement for RF test in scum_validation.py
2025-04-29 Corrected directory, csv, and png creation.
2025-04-29 Created global variable for time stamped path.
2025-04-29 Remove stub functions and update radio self-test implementation in scum_validation.py
2025-04-30 Remove unused BoardFiles directory
2025-04-30 Tested yepkit power cycle, added sleep(5) to wait for device to power up. Made text output more descriptive
2025-05-01 REV3 begin
2025-05-01 Update picoFW to include Enable(X_32)/Disable(X_33) commands
2025-05-01 picoFW disable all on init
2025-05-01 Fix naming; picoControl.py -> pico_control.py
2025-05-02 Radio test integrated. First working build
2025-05-02 Return structure corrections in RF_tx_rx_tests.py
2025-05-02 Remove unused import and clean up commented code in scum_validation.py
2025-05-02 Updated serial test return
2025-05-02 Add header block to email_report()
2025-05-02 yepkit will reset before power cycle
2025-05-03 Refactor RF_tx_rx_tests and scum_validation.py
2025-05-04 Add frequency conversion utility and update analog test outputs
2025-05-06 Bug fix Pluto file delete
2025-05-06 Remove restults from c source
2025-05-06 Add error handling to RF test to catch connection issues
2025-05-07 REV3 DRC pass
2025-05-08 Update RF_tx_rx_tests.py
    Increased Rx sample rate to better listen to scum radio and cleaned up sig figs in self test.
2025-05-12 Update RF_tx_rx_tests.py
    Implementing channel hopping to cover all of the scum sweep tones.
2025-05-14 Updated RF code for trigger handling to channel hop during scum sweep.
2025-05-14 Capitalized validation for importing "wait_for_trigger" function.
2025-05-14 Added dd_handle to radio communication test for trigger handling.
2025-05-14 radio test fixes - in progress
2025-05-14 Radio test success. Clean-up has not been done
2025-05-15 REV3 complete
2025-05-16 picoFW updates for PCB REV3
2025-05-20 Update config organization
2025-05-20 Enable option for email sending in nightly script
2025-05-20 update status messages
2025-05-20 New PCB fixes
2025-05-29 Updated radio code for creating LUT plot
2025-05-29 LUT plot updates
2025-06-03 Update docstring to clarify test_results argument structure requirements
2025-06-05 Add code and binary
2025-06-11 adjstmnts
2025-09-02 Push demo code
